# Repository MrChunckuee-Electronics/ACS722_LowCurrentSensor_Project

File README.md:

# ACS722 Low Current Sensor Project

***
Puedes seguirme en:
- [Blogspot](http://mrchunckuee.blogspot.com)
- [Instagram](https://www.instagram.com/mrchunckuee_electronics/)
- [Facebook](https://www.facebook.com/MrChunckueeElectronics)
- [Twitter](https://twitter.com/MrChunckuee)
- [YouTube](https://www.youtube.com/@MrChunckueeElectronics)

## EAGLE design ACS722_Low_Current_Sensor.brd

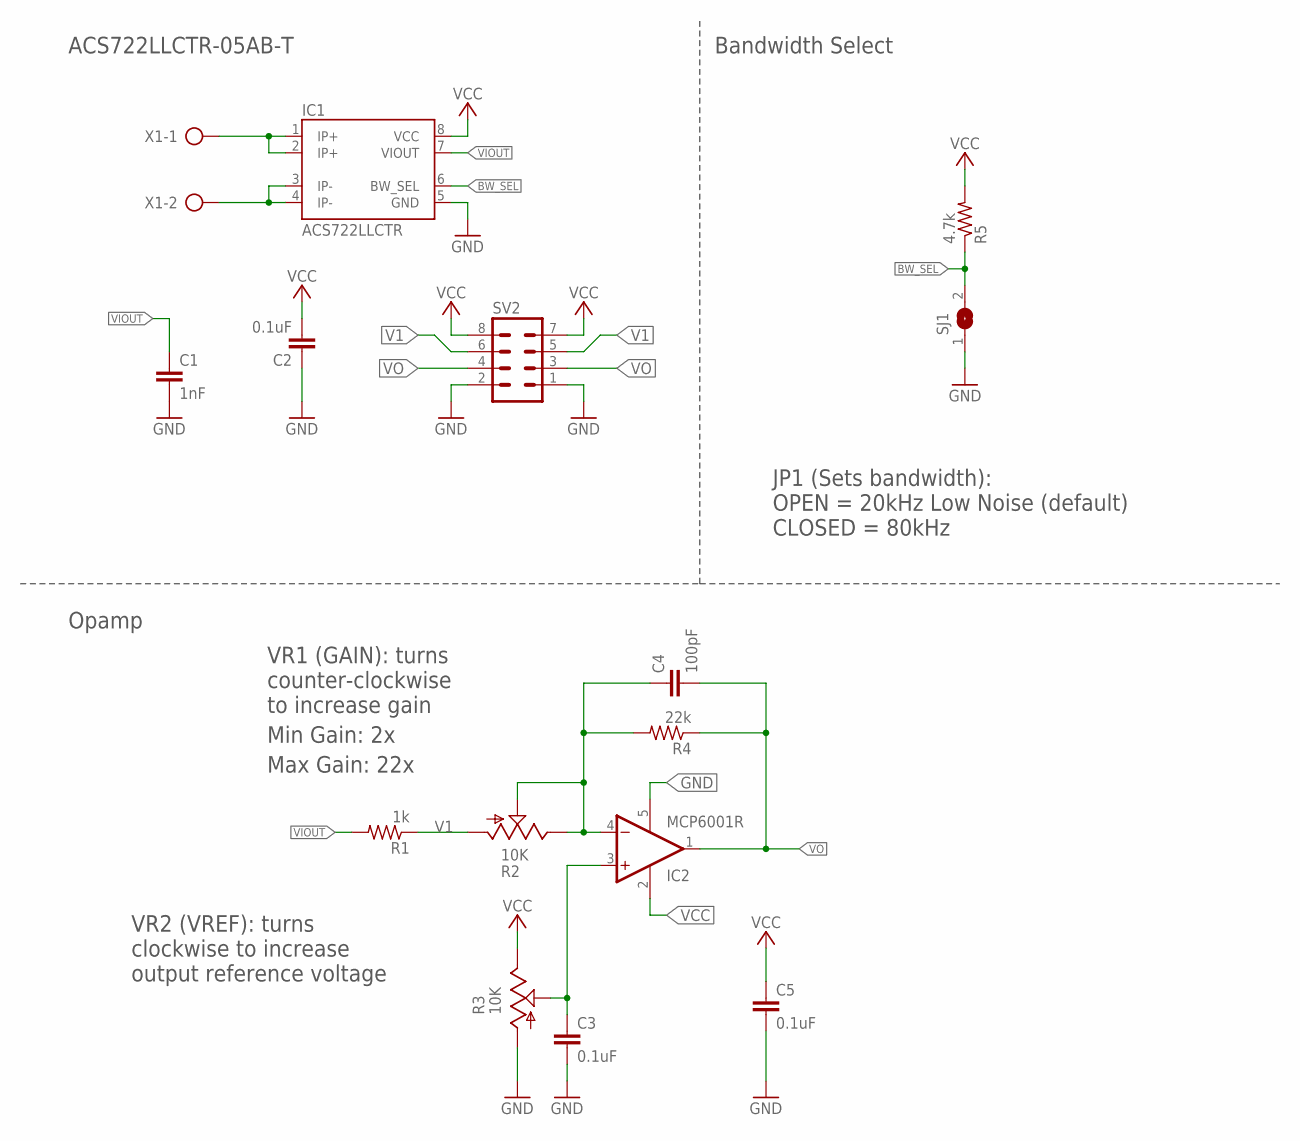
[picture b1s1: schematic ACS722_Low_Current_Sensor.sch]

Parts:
C1: 1nF; C1206
C2, C3, C5: 0.1uF; C1206
C4: 100pF; C1206
IC1: ACS722LLCTR; SO-08
IC2: MCP6001R; SOT23-5
R1: 1k; R1206
R2, R3: 10K; CA9V
R4: 22k; R1206
R5: 4.7k; R1206
SJ1: SJ
SV2: MA04-2
X1: AK500/2

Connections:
BW_SEL: IC1.6 (BW_SEL), R5.1, SJ1.2
GND: C1.2, C2.1, C3.2, C5.2, IC1.5 (GND), IC2.5 (V-), R3.A, SJ1.1, SV2.1, SV2.2
IP+: IC1.1 (IP+), IC1.2 (IP+), X1.1
IP-: IC1.3 (IP-), IC1.4 (IP-), X1.2
unnamed: C4.1, IC2.4 (-IN), R2.E, R2.S, R4.2
unnamed: C3.1, IC2.3 (+IN), R3.S
V1: R1.1, R2.A, SV2.5, SV2.6
VCC: C2.2, C5.1, IC1.8 (VCC), IC2.2 (V+), R3.E, R5.2, SV2.7, SV2.8
VIOUT: C1.1, IC1.7 (VIOUT), R1.2
VO: C4.2, IC2.1 (OUT), R4.1, SV2.3, SV2.4

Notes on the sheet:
Opamp
JP1 (Sets bandwidth):
CLOSED = 80kHz
OPEN = 20kHz Low Noise (default)
Bandwidth Select
VR1 (GAIN): turns counter-clockwise to increase gain
VR2 (VREF): turns clockwise to increase output reference voltage
ACS722LLCTR-05AB-T
Max Gain: 22x
Min Gain: 2x

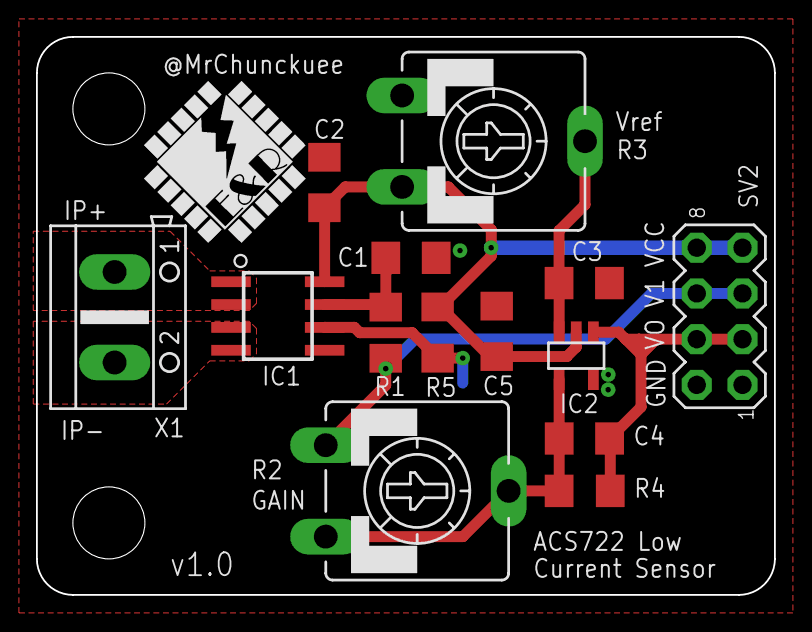
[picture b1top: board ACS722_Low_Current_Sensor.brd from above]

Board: 2 copper layers, 41.0 x 31.0 mm, 15 parts (1 on the bottom side), 10 nets.

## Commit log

2021-03-24 Created project
2021-03-24 Add GERBERs
2021-03-24 Respaldo GERBERs del HW v1.0
2021-03-24 Creación del hardware ACS22 Low Current Sensor v1.0
2021-07-11 Add assets
